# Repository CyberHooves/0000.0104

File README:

HAOS REDRO PN: 0000.0104
========================

This is a 1.2kW SMPS for audio amplifiers designed to fit within a 1U case.

Input: 400V DC
Output 1: +100V, 6A
Output 2: -100V, 6A
Output 3: +15V, 500mA
Output 4: -15V, 500mA
Output 5: +12V, 1A
Output 6: +12V, 500mA, referenced to Output 2.

The main outputs are unregulated and it is reccomended to use a suitable power factor correction circuit in applications where line regulation is necessary.
Auxiliary outputs 3 and 4 are provided for small-signal curcuits. Output 6 is provided for class-D amplifiers that require a gate drive supply referenced to the negative supply rail. 
Isolated and non-isolated inputs are provided to shut down the converter on J10 and J11, respectively. Oveheating protection is provided by a thermostat mounted on the heatsink.

This repository is released under CERN-OHL-S 2.0

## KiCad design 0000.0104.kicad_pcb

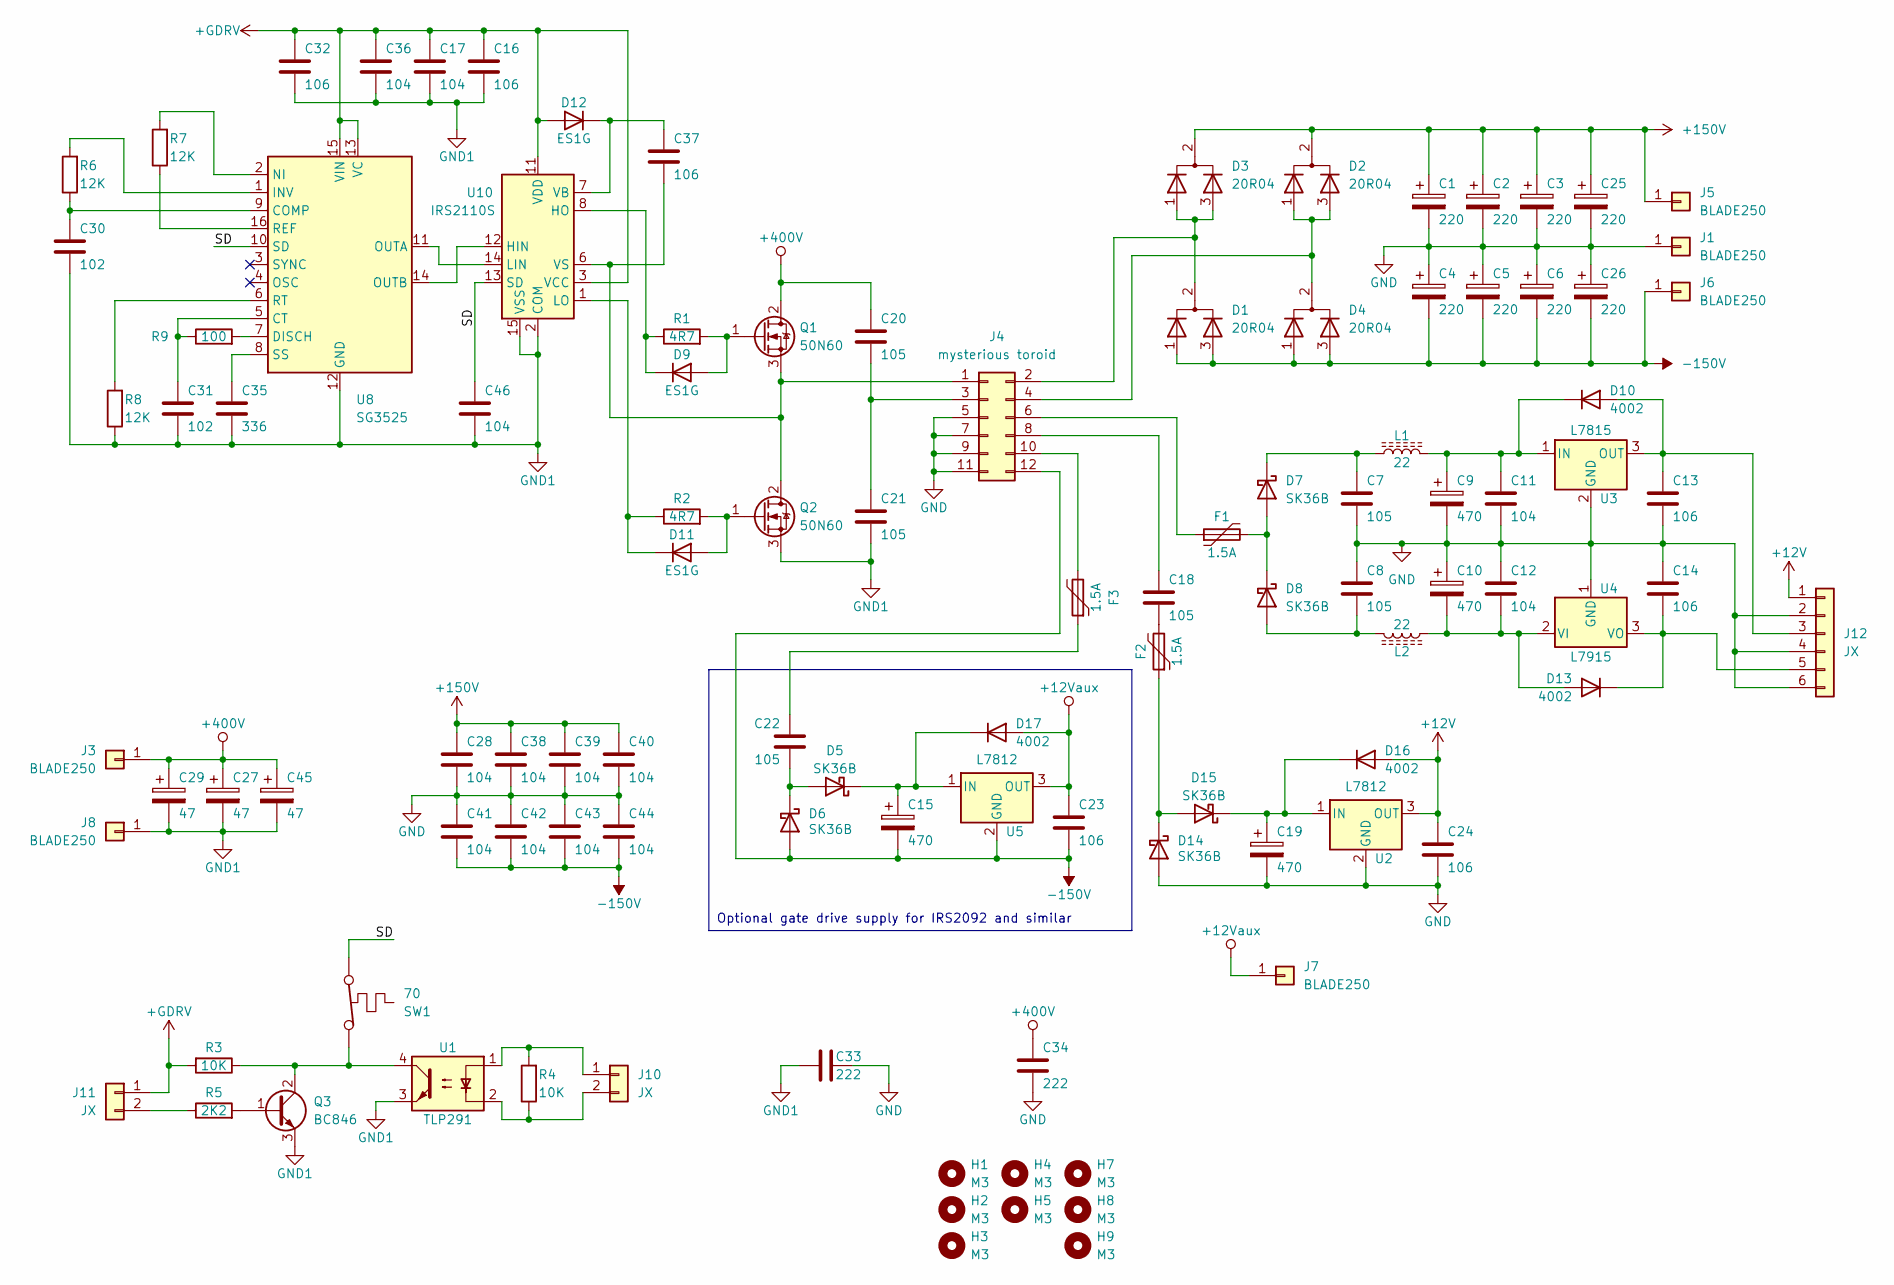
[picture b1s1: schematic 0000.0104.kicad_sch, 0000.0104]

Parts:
C1, C2, C3, C4, C5, C6, C25, C26: 220; CP_Radial_D16.0mm_P7.50mm
C7, C8, C18, C22: 105; C_1210_3225Metric
C9, C10, C15, C19: 470; CP_Radial_D10.0mm_P5.00mm
C11, C12, C17, C36, C46: 104; C_0805_2012Metric
C13, C14, C16, C23, C24, C32, C37: 106; C_1210_3225Metric
C20, C21: 105; C_Rect_L26.5mm_W11.5mm_P22.50mm_MKS4
C27, C29, C45: 47; CP_Radial_D18.0mm_P7.50mm
C28, C38, C39, C40, C41, C42, C43, C44: 104; C_1210_3225Metric
C30, C31: 102; C_0805_2012Metric
C33, C34: 222; C_Disc_D10.5mm_W5.0mm_P10.00mm
C35: 336; C_0805_2012Metric
D1, D2, D3, D4: 20R04; TO-220-3_Vertical_Staggered
D5, D6, D7, D8, D14, D15: SK36B; D_SMB
D9, D11, D12: ES1G; D_SMA
D10, D13, D16, D17: 4002; D_SMA
F1, F2, F3: 1.5A; Fuse_1210_3225Metric
H1, H2, H3, H4, H5, H7, H8, H9: M3; MountingHole_3.2mm_M3
J1, J3, J5, J6, J7, J8: BLADE250; CON-BLADE250-VERTICAL
J4: mysterious toroid; TRANSFORMER-TOROID-D55-H-8P-1
J10, J11: JX; JST_XA_B02B-XASK-1-A_1x02_P2.50mm_Vertical
J12: JX; JST_XA_B06B-XASK-1-A_1x06_P2.50mm_Vertical
L1, L2: 22; INDUCTOR_SMD_7x7
Q1, Q2: 50N60; TO-247-3_Vertical
Q3: BC846; SOT-23
R1, R2: 4R7; R_1210_3225Metric
R3, R4: 10K; R_0805_2012Metric
R5: 2K2; R_0805_2012Metric
R6, R7, R8: 12K; R_0805_2012Metric
R9: 100; R_0805_2012Metric
SW1: 70; TO-220-2_Vertical
U1: TLP291; DIP-4_W10.16mm
U2, U5: L7812; TO-220-3_Vertical
U3: L7815; TO-220-3_Vertical
U4: L7915; TO-220-3_Vertical
U8: SG3525; SO-16_3.9x9.9mm_P1.27mm
U10: IRS2110S; SOIC-16W_7.5x10.3mm_P1.27mm

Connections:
+12V: C24.1, D16.2 (A), J12.1, U2.3 (OUT)
+12Vaux: C23.1, D17.2 (A), J7.1, U5.3 (OUT)
+150V: C1.1, C2.1, C3.1, C25.1, C28.1, C38.1, C39.1, C40.1, D2.2 (A), D3.2 (A), J5.1
+400V: C20.1, C27.1, C29.1, C34.1, C45.1, J3.1, Q1.2 (D)
+GDRV: C16.1, C17.1, C32.1, C36.1, D12.2 (A), J11.1, R3.2, U8.13 (VC), U8.15 (VIN), U10.3 (VCC), U10.11 (VDD)
-150V: C4.2, C5.2, C6.2, C15.2, C23.2, C26.2, C41.2, C42.2, C43.2, C44.2, D1.1 (K), D1.3 (K), D4.1 (K), D4.3 (K), D6.2 (A), J4.12, J6.1, U5.2 (GND)
/SD: C46.1, SW1.1, U8.10 (SD), U10.13 (SD)
GND: C1.2, C2.2, C3.2, C4.1, C5.1, C6.1, C7.2, C8.1, C9.2, C10.1, C11.2, C12.1, C13.2, C14.1, C19.2, C24.2, C25.2, C26.1, C28.2, C33.2, C34.2, C38.2, C39.2, C40.2, C41.1, C42.1, C43.1, C44.1, D14.2 (A), J1.1, J4.5, J4.7, J4.9, J4.11, J12.2, J12.4, J12.6, U2.2 (GND), U3.2 (GND), U4.1 (GND)
GND1: C16.2, C17.2, C21.2, C27.2, C29.2, C30.2, C31.2, C32.2, C33.1, C35.2, C36.2, C45.2, C46.2, J8.1, Q2.3 (S), Q3.3 (E), R8.1, U1.3, U8.12 (GND), U10.2 (COM), U10.15 (VSS)
unnamed: C18.1, F2.2
unnamed: C22.2, F3.1
unnamed: D1.2 (A), D3.1 (K), D3.3 (K), J4.2
unnamed: D2.1 (K), D2.3 (K), D4.2 (A), J4.4
unnamed: C22.1, D5.2 (A), D6.1 (K)
unnamed: D7.2 (A), D8.1 (K), F1.2
unnamed: C7.1, D7.1 (K), L1.1
unnamed: C8.2, D8.2 (A), L2.1
unnamed: D9.2 (A), Q1.1 (G), R1.2
unnamed: D9.1 (K), R1.1, U10.8 (HO)
unnamed: C13.1, D10.2 (A), J12.3, U3.3 (OUT)
unnamed: C9.1, C11.1, D10.1 (K), L1.2, U3.1 (IN)
unnamed: D11.2 (A), Q2.1 (G), R2.2
unnamed: D11.1 (K), R2.1, U10.1 (LO)
unnamed: C37.1, D12.1 (K), U10.7 (VB)
unnamed: C10.2, C12.2, D13.2 (A), L2.2, U4.2 (VI)
unnamed: C14.2, D13.1 (K), J12.5, U4.3 (VO)
unnamed: D14.1 (K), D15.2 (A), F2.1
unnamed: C19.1, D15.1 (K), D16.1 (K), U2.1 (IN)
unnamed: C15.1, D5.1 (K), D17.1 (K), U5.1 (IN)
unnamed: C37.2, J4.1, Q1.3 (S), Q2.2 (D), U10.6 (VS)
unnamed: C20.2, C21.1, J4.3
unnamed: F1.1, J4.6
unnamed: C18.2, J4.8
unnamed: F3.2, J4.10
unnamed: J10.1, R4.2, U1.1
unnamed: J10.2, R4.1, U1.2
unnamed: J11.2, R5.1
unnamed: Q3.1 (B), R5.2
unnamed: Q3.2 (C), R3.1, SW1.2, U1.4
unnamed: C30.1, R6.1, U8.9 (COMP)
unnamed: C31.1, R9.1, U8.5 (CT)
unnamed: R9.2, U8.7 (DISCH)
unnamed: R6.2, U8.1 (INV)
unnamed: R7.2, U8.2 (NI)
unnamed: R7.1, U8.16 (REF)
unnamed: R8.2, U8.6 (RT)
unnamed: C35.1, U8.8 (SS)
unnamed: U8.14 (OUTB), U10.12 (HIN)
unnamed: U8.11 (OUTA), U10.14 (LIN)

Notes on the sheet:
Optional gate drive supply for IRS2092 and similar

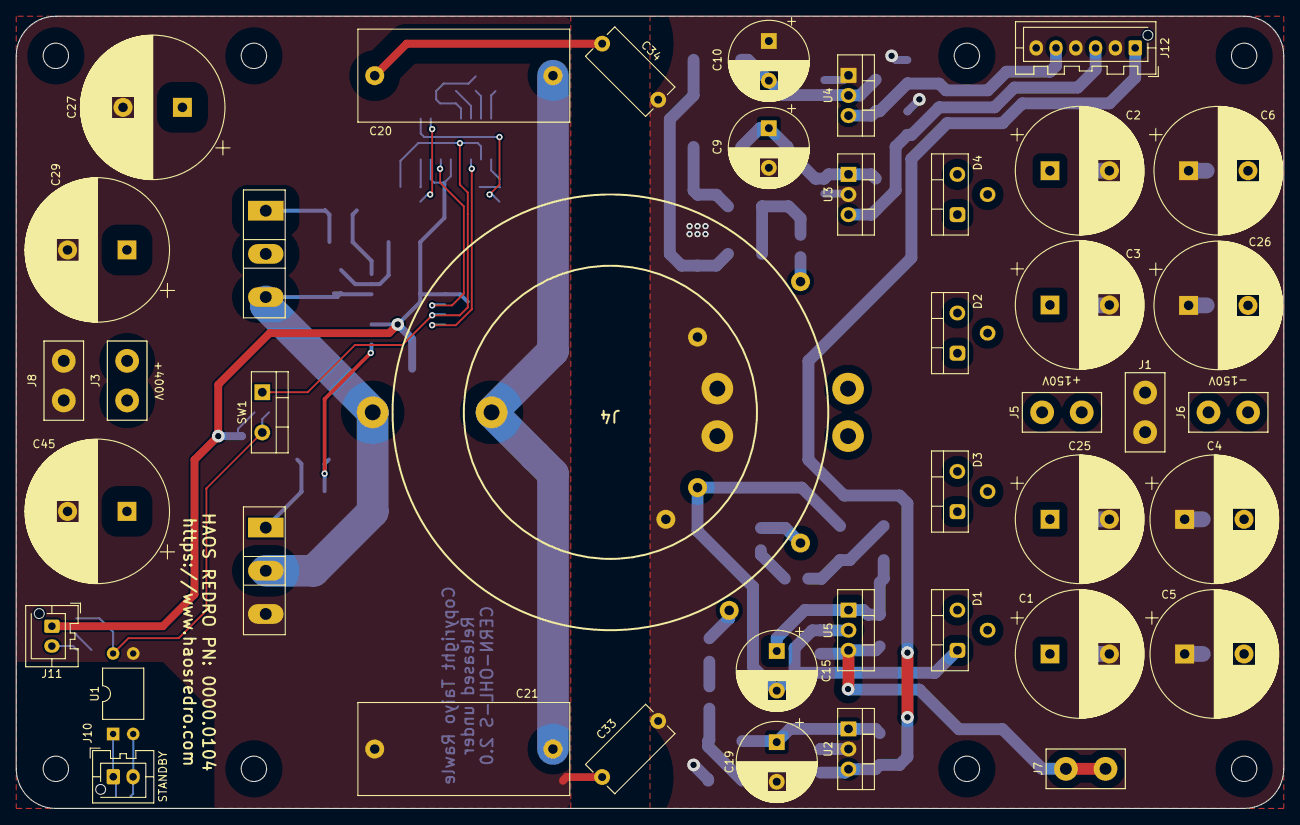
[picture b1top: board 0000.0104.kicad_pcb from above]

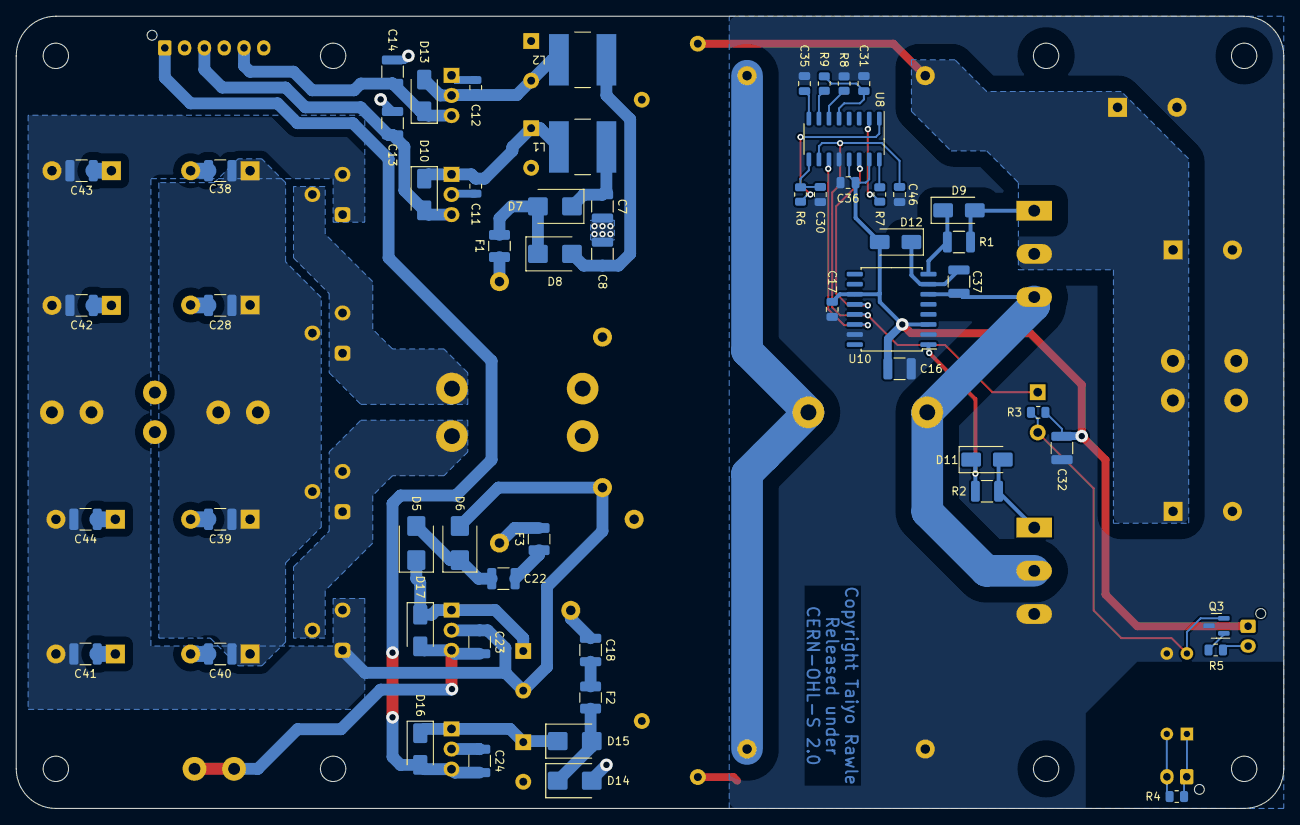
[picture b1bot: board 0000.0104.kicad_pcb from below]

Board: 2 copper layers, 160.0 x 100.0 mm, 106 parts (57 on the bottom side), 49 nets.

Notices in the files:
0000.0104.kicad_pcb:
Copyright Taiyo Rawle
Released under
CERN-OHL-S 2.0
0000.0104.kicad_sch:
Released under CERN OHL 2.0-S
